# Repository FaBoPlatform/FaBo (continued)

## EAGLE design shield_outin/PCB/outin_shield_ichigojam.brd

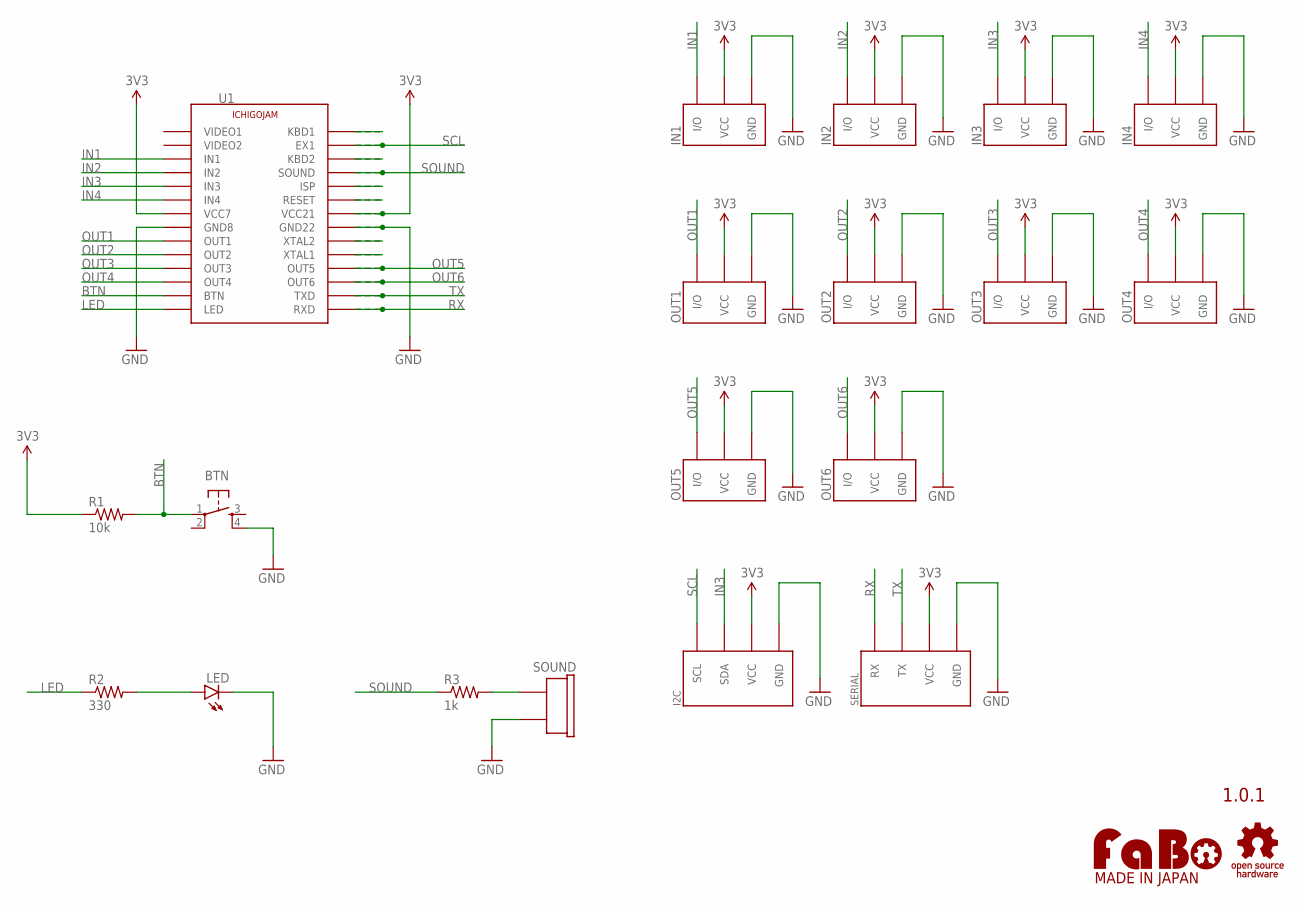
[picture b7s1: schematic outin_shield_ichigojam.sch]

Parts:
BTN: SWITCH-TACT-12MM; 1273HA-160G-G
I2C: FABO_BRICK_I2C-CONNECTOR; FABO_BRICK_I2C_CONNECTOR
IN1, IN2, IN3, IN4: FABO_BRICK_3PIN-CONNECTOR; FABO_BRICK_3PIN_CONNECTOR
LED: LED-5MM
OUT1, OUT2, OUT3, OUT4: FABO_BRICK_3PIN-CONNECTOR; FABO_BRICK_3PIN_CONNECTOR
OUT5, OUT6: FABO_BRICK_3PIN-HEADER; FABO_BRICK_3PIN_HEADER
R1: 10k; RES-AXL-REGULAR
R2: 330; RES-AXL-REGULAR
R3: 1k; RES-AXL-REGULAR
SERIAL: FABO_BRICK_SERIAL-CONNECTOR; FABO_BRICK_SERIAL_CONNECTOR
SOUND: BUZZER-PKM13EPYH4000; PKM13EPYH4000-A0
U1: ICHIGOJAM_SHIELD; ICHIGOJAM_SHIELD_HOLE_DIM
U$2: LOGO_OSHW-T_M; LOGO_OSHW_T_M
U$3: LOGO_FABO-M; LOGO_FABO_M

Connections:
3V3: I2C.VCC, IN1.VCC, IN2.VCC, IN3.VCC, IN4.VCC, OUT1.VCC, OUT2.VCC, OUT3.VCC, OUT4.VCC, OUT5.VCC, OUT6.VCC, R1.P$1 (1), SERIAL.VCC, U1.VCC7, U1.VCC21, U1.VCC21-2
BTN: BTN.1, R1.P$2 (2), U1.BTN
GND: BTN.4, I2C.GND, IN1.GND, IN2.GND, IN3.GND, IN4.GND, LED.K (C), OUT1.GND, OUT2.GND, OUT3.GND, OUT4.GND, OUT5.GND, OUT6.GND, SERIAL.GND, SOUND.2, U1.GND8, U1.GND22, U1.GND22-2
IN1: IN1.IN/OUT (I/O), U1.IN1
IN2: IN2.IN/OUT (I/O), U1.IN2
IN3: I2C.SDA, IN3.IN/OUT (I/O), U1.IN3
IN4: IN4.IN/OUT (I/O), U1.IN4
LED: R2.P$1 (1), U1.LED
unnamed: LED.A, R2.P$2 (2)
unnamed: R3.P$2 (2), SOUND.1
unnamed: U1.KBD1, U1.KBD1-2
unnamed: U1.KBD2, U1.KBD2-2
unnamed: U1.ISP, U1.ISP-2
unnamed: U1.RESET, U1.RESET-2
unnamed: U1.XTAL2, U1.XTAL2-2
unnamed: U1.XTAL1, U1.XTAL1-2
OUT1: OUT1.IN/OUT (I/O), U1.OUT1
OUT2: OUT2.IN/OUT (I/O), U1.OUT2
OUT3: OUT3.IN/OUT (I/O), U1.OUT3
OUT4: OUT4.IN/OUT (I/O), U1.OUT4
OUT5: OUT5.I/O, U1.OUT5, U1.OUT5-2
OUT6: OUT6.I/O, U1.OUT6, U1.OUT6-2
RX: SERIAL.RX, U1.RXD, U1.RXD-2
SCL: I2C.SCL, U1.EX1, U1.EX1-2
SOUND: R3.P$1 (1), U1.SOUND, U1.SOUND-2
TX: SERIAL.TX, U1.TXD, U1.TXD-2

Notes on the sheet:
1.0.1

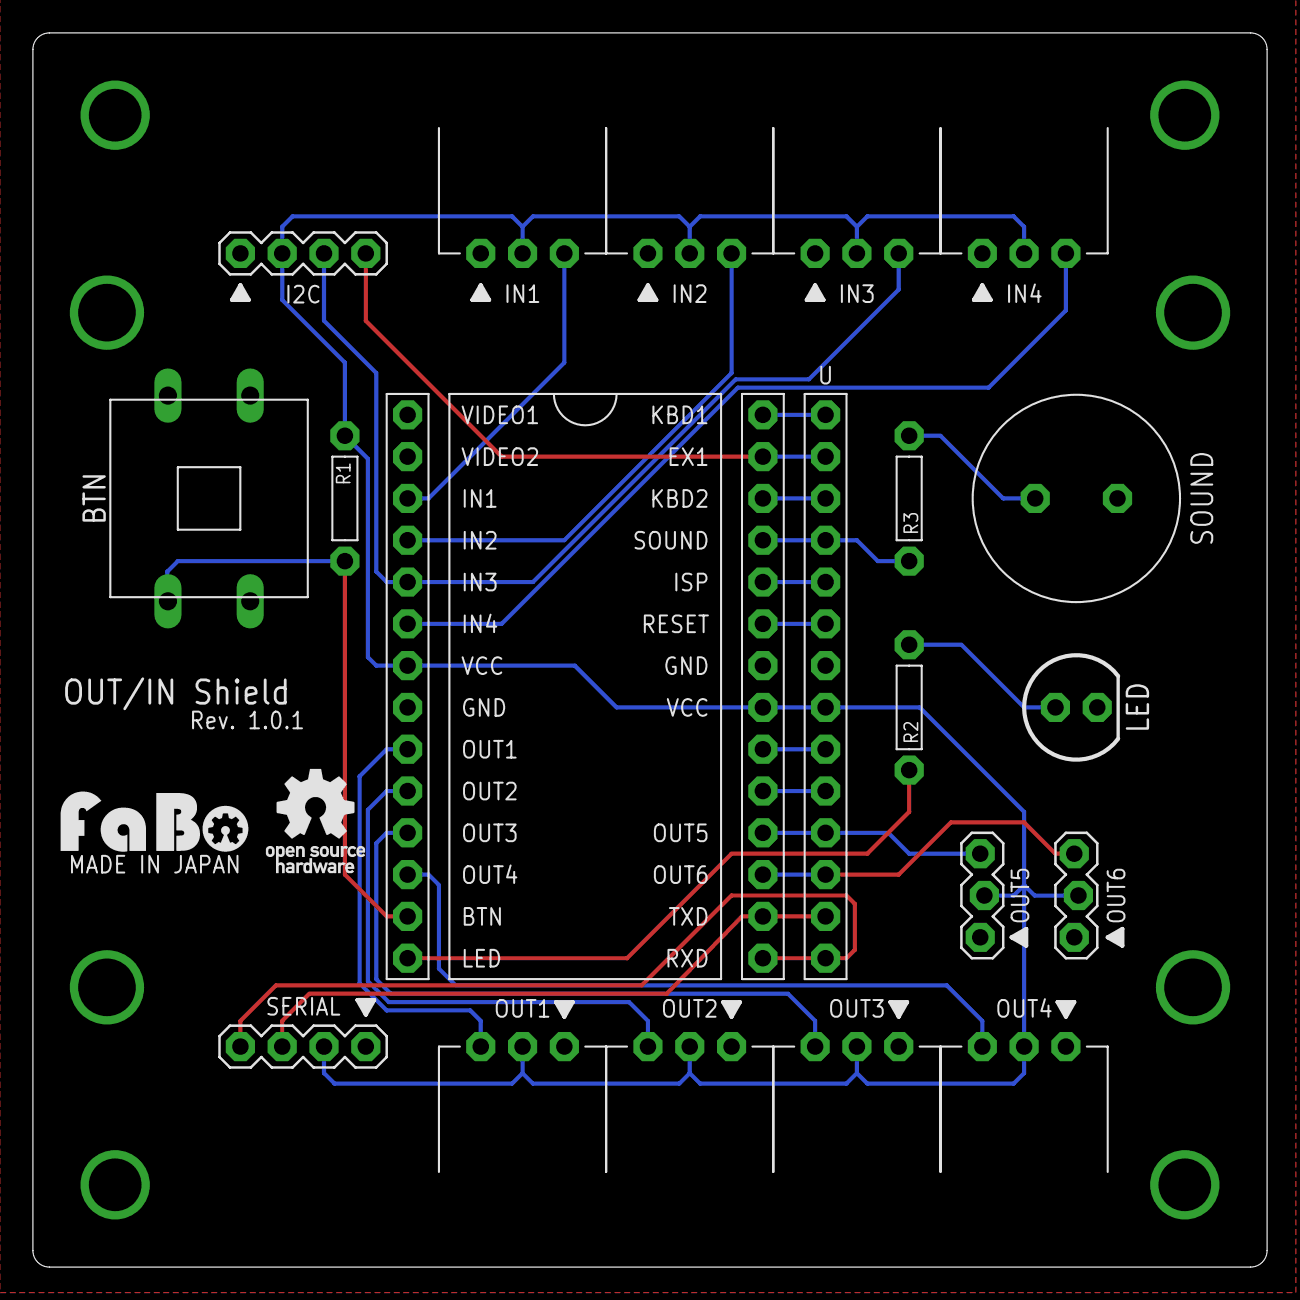
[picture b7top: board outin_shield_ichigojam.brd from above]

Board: 2 copper layers, 75.0 x 75.0 mm, 21 parts (0 on the bottom side), 26 nets.

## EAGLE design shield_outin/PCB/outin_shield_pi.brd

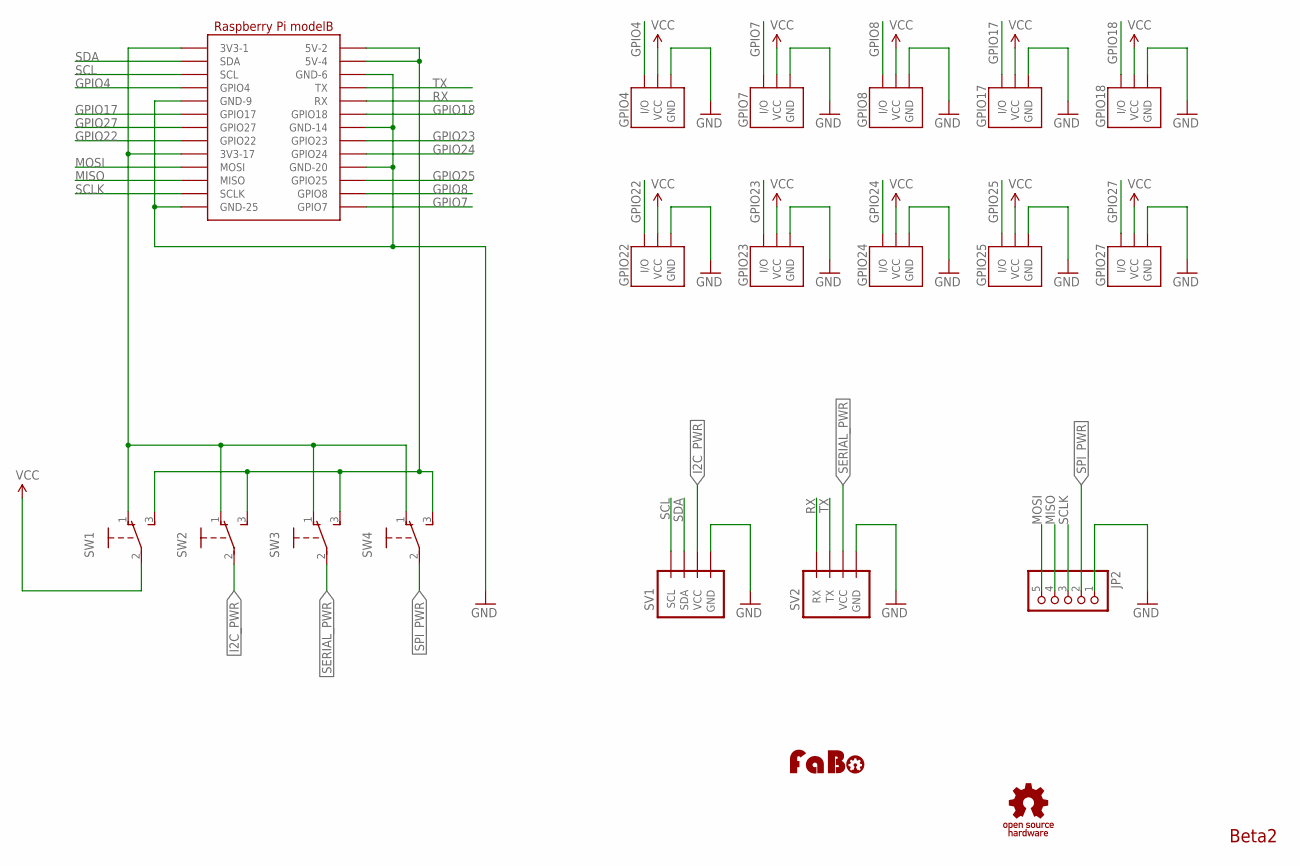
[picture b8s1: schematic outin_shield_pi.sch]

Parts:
GPIO4, GPIO7, GPIO8, GPIO17, GPIO18, GPIO22, GPIO23, GPIO24, GPIO25, GPIO27: IO_PIN-3PIN; 1X3-SNEAKY
JP2: PINHD-1X5; 1X05
SV1: BRICK_I2C_CONNECTOR
SV2: BRICK_SERIAL_CONNECTOR
SW1, SW2, SW3, SW4: SWITCH-SLIDE-EG1218; EG1218
U1: RASPBERRY_PI_B1; RASPBERRY_PI_B
U$14: LOGO_FABO-M; LOGO_FABO_M
U$15: LOGO_OSHW_T-M; LOGO_OSHW_T_M

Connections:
3V3: SW1.1, SW2.1, SW3.1, SW4.1, U1.1 (3V3-1), U1.17 (3V3-17)
5V: SW1.3, SW2.3, SW3.3, SW4.3, U1.2 (5V-2), U1.4 (5V-4)
GND: GPIO4.1 (GND), GPIO7.1 (GND), GPIO8.1 (GND), GPIO17.1 (GND), GPIO18.1 (GND), GPIO22.1 (GND), GPIO23.1 (GND), GPIO24.1 (GND), GPIO25.1 (GND), GPIO27.1 (GND), JP2.1, SV1.GND, SV2.GND, U1.6 (GND-6), U1.9 (GND-9), U1.14 (GND-14), U1.20 (GND-20), U1.25 (GND-25)
GPIO4: GPIO4.3 (I/O), U1.7 (GPIO4)
GPIO7: GPIO7.3 (I/O), U1.26 (GPIO7)
GPIO8: GPIO8.3 (I/O), U1.24 (GPIO8)
GPIO17: GPIO17.3 (I/O), U1.11 (GPIO17)
GPIO18: GPIO18.3 (I/O), U1.12 (GPIO18)
GPIO22: GPIO22.3 (I/O), U1.15 (GPIO22)
GPIO23: GPIO23.3 (I/O), U1.16 (GPIO23)
GPIO24: GPIO24.3 (I/O), U1.18 (GPIO24)
GPIO25: GPIO25.3 (I/O), U1.22 (GPIO25)
GPIO27: GPIO27.3 (I/O), U1.13 (GPIO27)
I2C_PWR: SV1.VCC, SW2.2
MISO: JP2.4, U1.21 (MISO)
MOSI: JP2.5, U1.19 (MOSI)
RX: SV2.RX, U1.10 (RX)
SCL: SV1.SCL, U1.5 (SCL)
SCLK: JP2.3, U1.23 (SCLK)
SDA: SV1.SDA, U1.3 (SDA)
SERIAL_PWR: SV2.VCC, SW3.2
SPI_PWR: JP2.2, SW4.2
TX: SV2.TX, U1.8 (TX)
VCC: GPIO4.2 (VCC), GPIO7.2 (VCC), GPIO8.2 (VCC), GPIO17.2 (VCC), GPIO18.2 (VCC), GPIO22.2 (VCC), GPIO23.2 (VCC), GPIO24.2 (VCC), GPIO25.2 (VCC), GPIO27.2 (VCC), SW1.2

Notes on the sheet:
Beta2

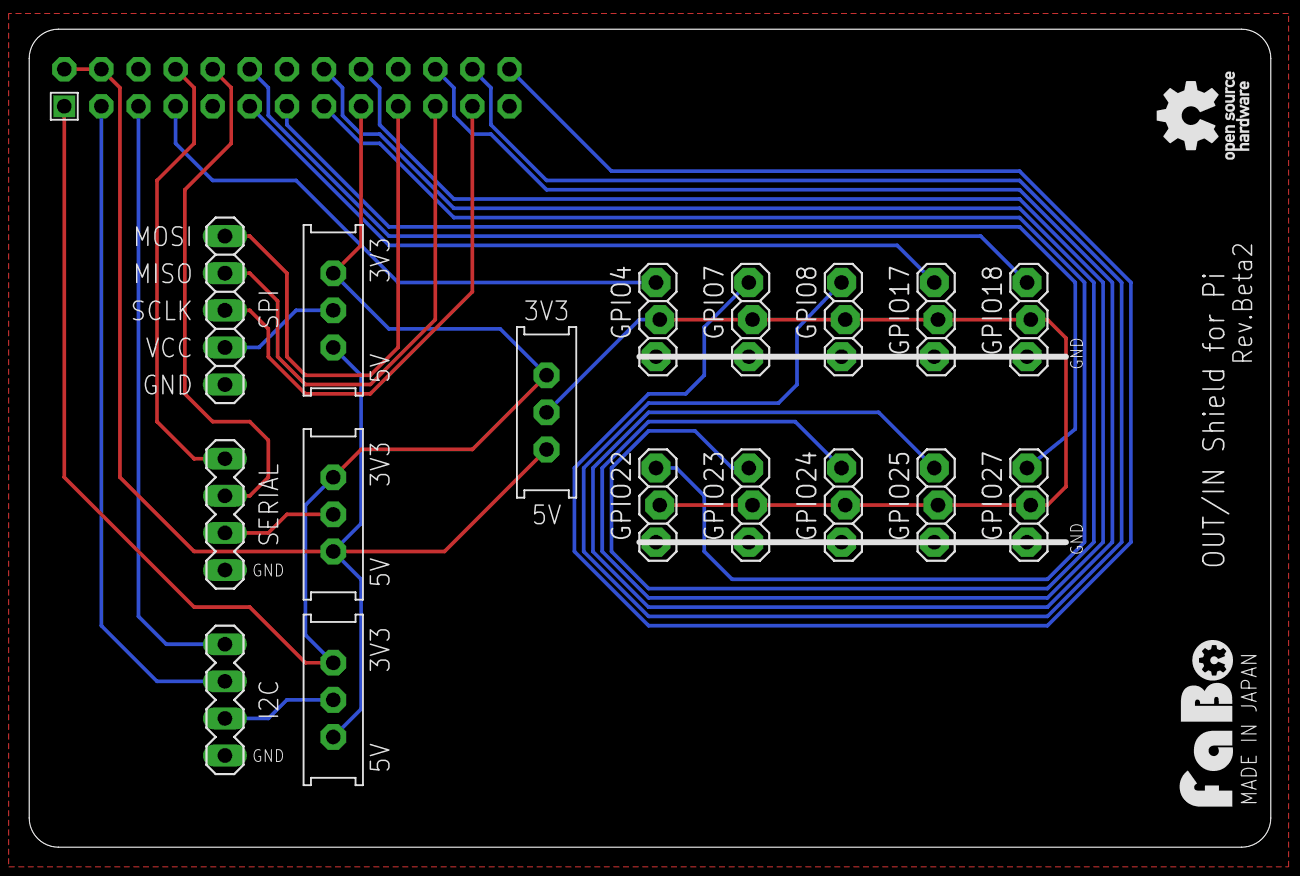
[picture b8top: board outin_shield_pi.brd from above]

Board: 2 copper layers, 85.0 x 56.0 mm, 20 parts (0 on the bottom side), 24 nets.
